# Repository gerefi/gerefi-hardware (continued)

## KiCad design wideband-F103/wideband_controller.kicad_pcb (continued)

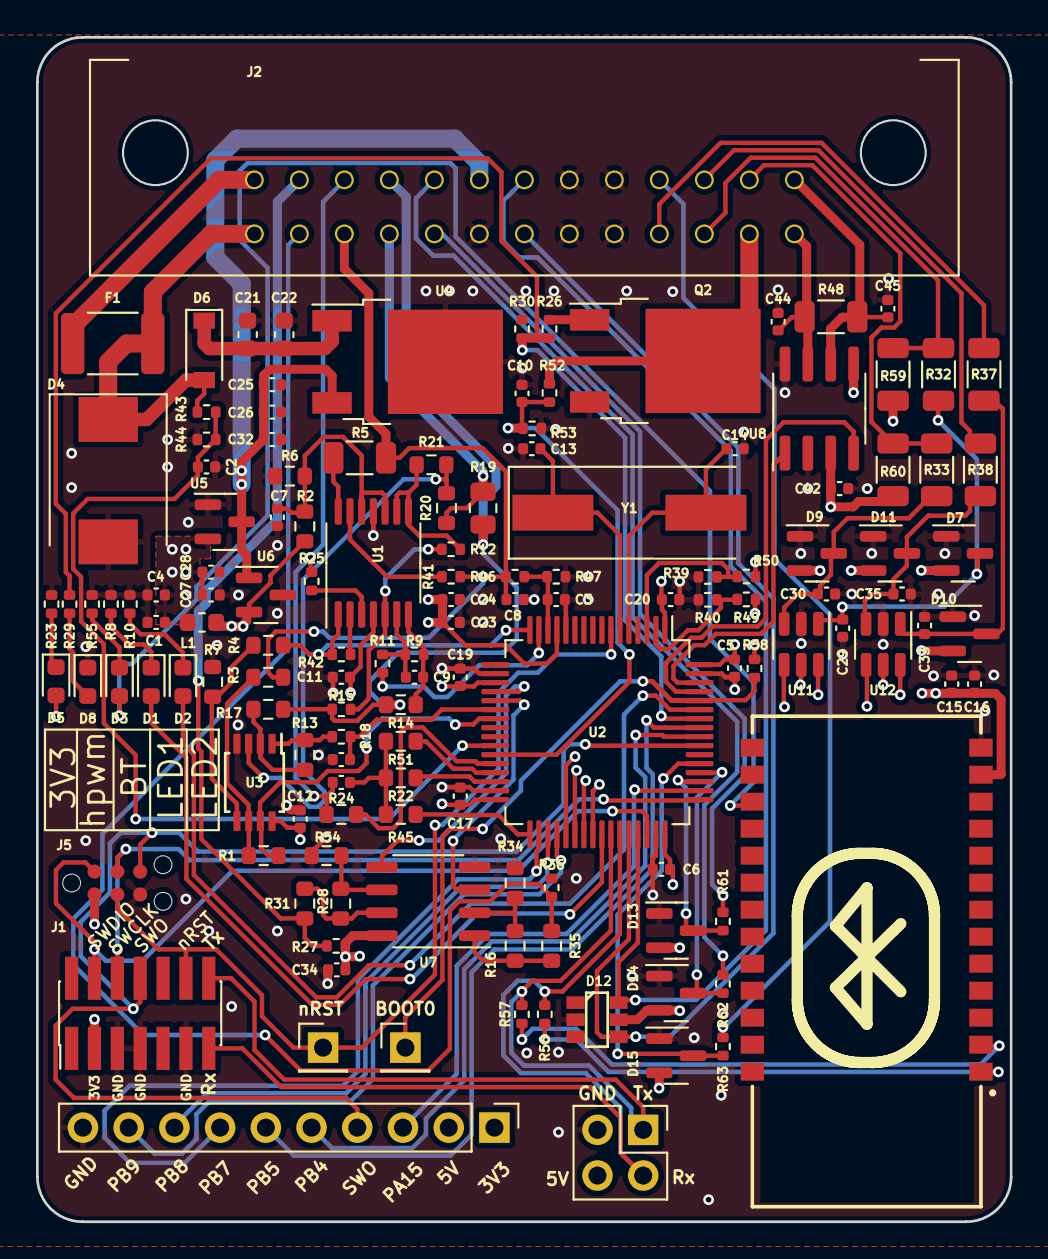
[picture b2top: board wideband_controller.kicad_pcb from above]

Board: 4 copper layers, 54.1 x 65.8 mm, 138 parts (0 on the bottom side), 99 nets.

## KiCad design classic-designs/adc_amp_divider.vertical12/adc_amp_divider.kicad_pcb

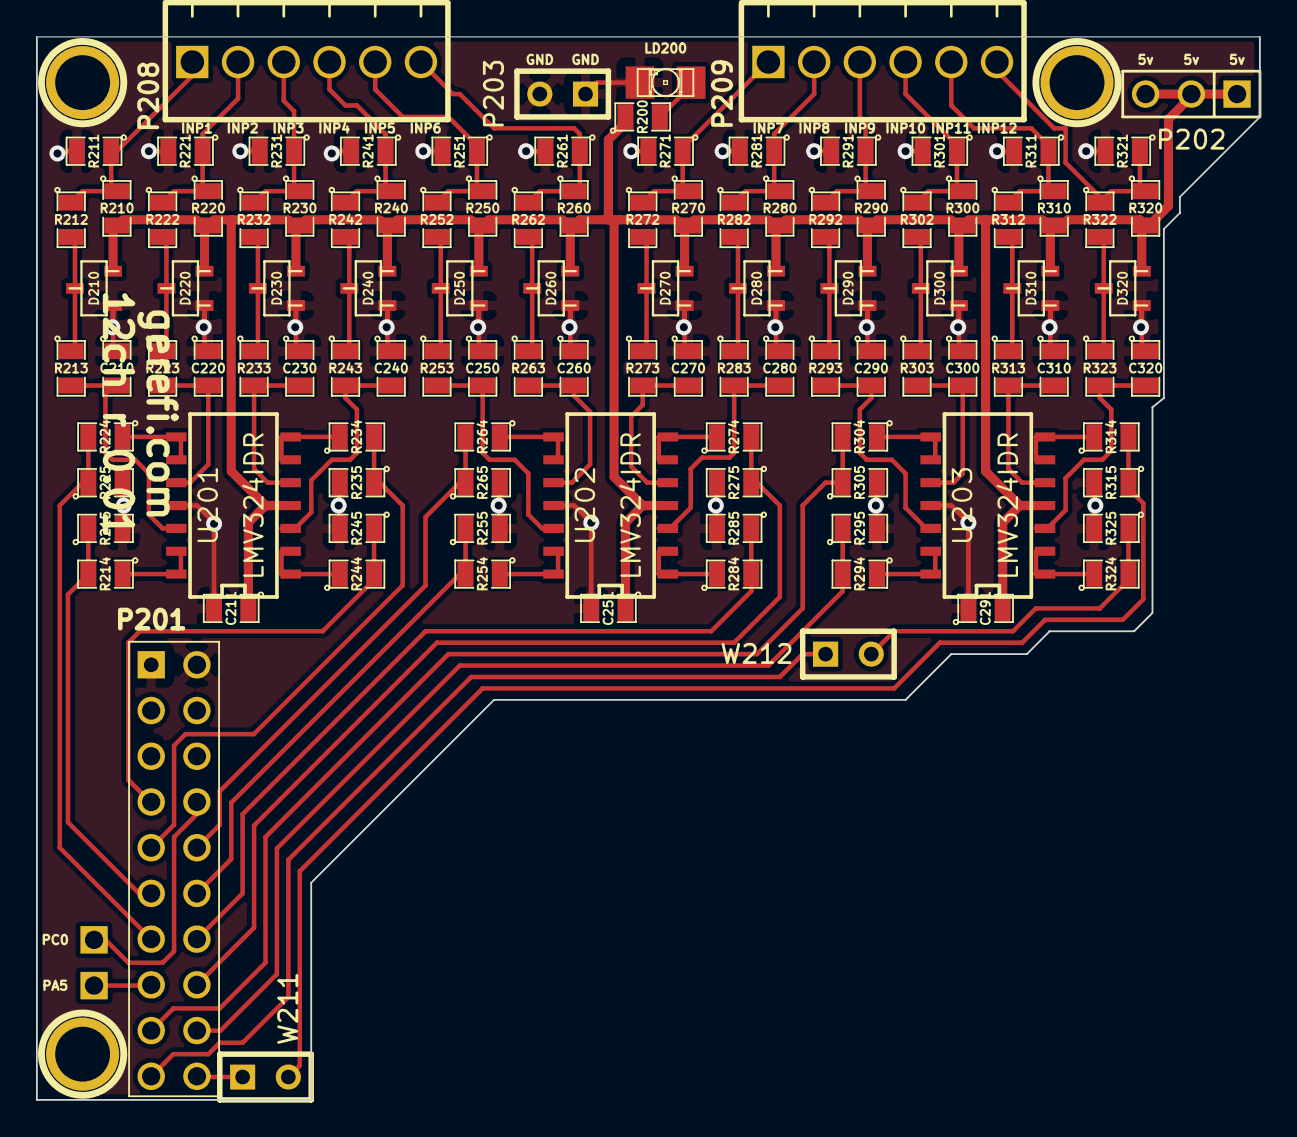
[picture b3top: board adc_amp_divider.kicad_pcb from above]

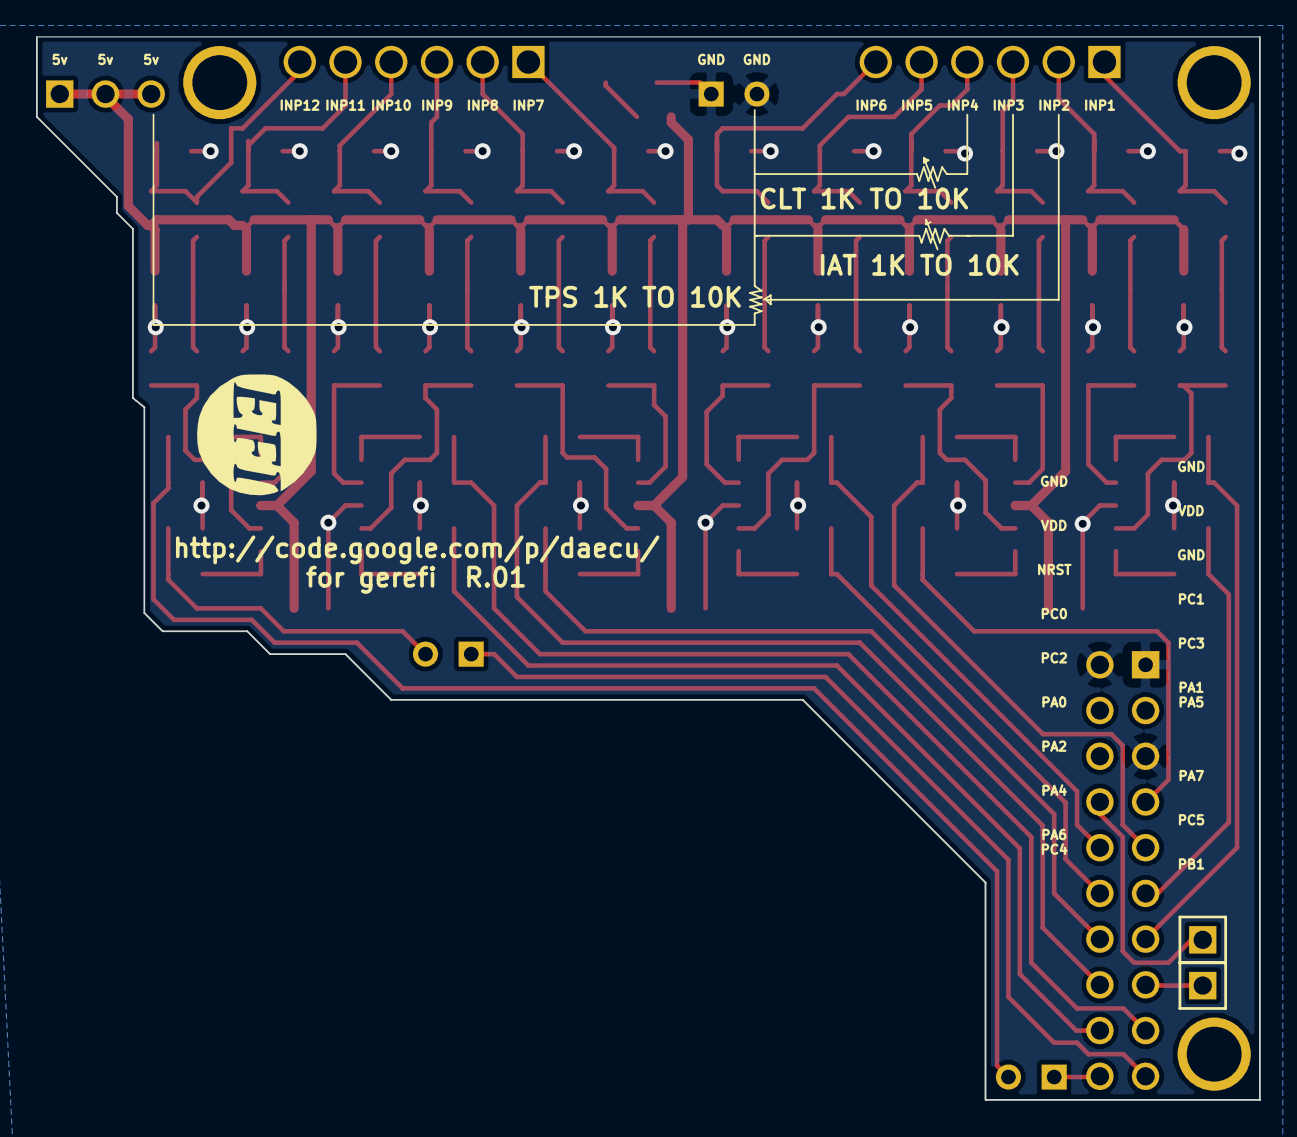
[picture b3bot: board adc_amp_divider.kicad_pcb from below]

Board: 2 copper layers, 67.9 x 59.1 mm, 117 parts (3 on the bottom side), 67 nets.

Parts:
C210, C220, C230, C240, C250, C260, C270, C280, C290, C300, C310, C320: 0.01uF; SM0805
C211, C251, C291: 0.1uF; SM0805
D210, D220, D230, D240, D250, D260, D270, D280, D290, D300, D310, D320: DOUBLE_SCHOTTKY; sot23
G201: LOGO; LOGO_F
LD200: LED; LED-1206
M200, M201, M202: CONN_1; 1pin
P201: CONN_10X2; PIN_ARRAY_10X2_M
P202: CONN_3; PIN_ARRAY_3X1
P203: CONN_2; SIL-2
P204, P205: CONN_1; PIN_ARRAY_1
P208, P209: CONN_6; 6_screw_term_.1in
R200, R213, R223, R233, R243, R253, R263, R273, R283, R293, R303, R313, R323: 100; SM0805
R210, R220, R230, R240, R250, R260, R270, R280, R290, R300, R310, R320: 2700; SM0805
R211, R221, R231, R241, R251, R261, R271, R281, R291, R301, R311, R321: 500K; SM0805
R212, R222, R232, R242, R252, R262, R272, R282, R292, R302, R312, R322: 10k; SM0805
R214, R215, R224, R225, R234, R235, R244, R245, R254, R255, R264, R265, R274, R275, R284, R285, R294, R295, R304, R305, R314, R315, R324, R325: 1500; SM0805
U201, U202, U203: LMV324IDR; SO14N
W211, W212: TEST; SIL-2

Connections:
/5V: C211.1, C251.1, C291.2, D210.3, D220.3, D230.3, D240.3, D250.3, D260.3, D270.3, D280.3, D290.3, D300.3, D310.3, D320.3, P202.1, P202.2, P202.3, R200.1, R210.2, R220.2, R230.2, R240.2, R250.2, R260.2, R270.2, R280.2, R290.2, R300.2, R310.2, R320.2, U201.4, U202.4, U203.4
/INP1: P208.1, R210.1, R211.1, R212.1
/INP2: P208.2, R220.1, R221.1, R222.1
/INP3: P208.3, R230.1, R231.1, R232.1
/INP4: P208.4, R240.1, R241.1, R242.1
/INP5: P208.5, R250.1, R251.1, R252.1
/INP6: P208.6, R260.1, R261.1, R262.1
/INP7: P209.1, R270.1, R271.1, R272.1
/INP8: P209.2, R280.1, R281.1, R282.1
/INP9: P209.3, R290.1, R291.1, R292.1
/INP10: P209.4, R300.1, R301.1, R302.1
/INP11: P209.5, R310.1, R311.1, R312.1
/INP12: P209.6, R320.1, R321.1, R322.1
/OUT1: P201.11, R214.2, R215.1
/OUT2: P201.13, R224.2, R225.1
/OUT3: P201.9, R234.2, R235.1
/OUT4: P201.7, R244.2, R245.1
/OUT5: P201.12, R254.2, R255.1
/OUT6: P201.10, R264.2, R265.1
/OUT7: P201.16, R274.2, R275.1
/OUT8: P201.14, R284.2, R285.1
/OUT9: P201.18, R294.2, R295.1
/OUT10: P201.17, R304.2, R305.1
/OUT11: P201.20, W211.1
/OUT12: P201.19, W212.1
/PA5: P201.15, P204.1
/PC0: P201.8, P205.1
GND: C210.1, C211.2, C220.1, C230.1, C240.1, C250.1, C251.2, C260.1, C270.1, C280.1, C290.1, C291.1, C300.1, C310.1, C320.1, D210.1, D220.1, D230.1, D240.1, D250.1, D260.1, D270.1, D280.1, D290.1, D300.1, D310.1, D320.1, LD200.2, P201.1, P201.2, P201.5, P203.1, P203.2, R211.2, R215.2, R221.2, R225.2, R231.2, R235.2, R241.2, R245.2, R251.2, R255.2, R261.2, R265.2, R271.2, R275.2, R281.2, R285.2, R291.2, R295.2, R301.2, R305.2, R311.2, R315.2, R321.2, R325.2, U201.11, U202.11, U203.11
unnamed: D250.2, R252.2, R253.1
unnamed: D260.2, R262.2, R263.1
unnamed: D210.2, R212.2, R213.1
unnamed: D220.2, R222.2, R223.1
unnamed: D280.2, R282.2, R283.1
unnamed: R214.1, U201.13, U201.14
unnamed: R224.1, U201.8, U201.9
unnamed: D270.2, R272.2, R273.1
unnamed: R244.1, U201.1, U201.2
unnamed: D300.2, R302.2, R303.1
unnamed: D290.2, R292.2, R293.1
unnamed: R304.1, U203.8, U203.9
unnamed: R294.1, U203.13, U203.14
unnamed: C290.2, R293.2, U203.12
unnamed: C300.2, R303.2, U203.10
unnamed: R314.1, U203.6, U203.7
unnamed: R324.1, U203.1, U203.2
unnamed: C310.2, R313.2, U203.5
unnamed: C320.2, R323.2, U203.3
unnamed: D320.2, R322.2, R323.1
unnamed: D310.2, R312.2, R313.1
unnamed: R324.2, R325.1, W212.2
unnamed: R314.2, R315.1, W211.2
unnamed: C250.2, R253.2, U202.12
unnamed: R254.1, U202.13, U202.14
unnamed: R274.1, U202.6, U202.7
unnamed: R264.1, U202.8, U202.9
unnamed: C240.2, R243.2, U201.3
unnamed: C230.2, R233.2, U201.5
unnamed: C270.2, R273.2, U202.5
unnamed: C280.2, R283.2, U202.3
unnamed: C220.2, R223.2, U201.10
unnamed: C210.2, R213.2, U201.12
unnamed: C260.2, R263.2, U202.10
unnamed: R284.1, U202.1, U202.2
unnamed: D240.2, R242.2, R243.1
unnamed: LD200.1, R200.2
unnamed: D230.2, R232.2, R233.1
unnamed: R234.1, U201.6, U201.7

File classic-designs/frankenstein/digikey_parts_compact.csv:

### this file was generated by gerefi bom_builder on Sat Feb 22 11:01:39 CST 2014
### 292 components in 2047 lines of frankenstein.cmp
### 65 kinds of components in input file
### 9 entries in BOM dictionary bom_dictionary_digikey.csv
### 2 entries in ignore list
### no BOM record for 1pin_CONN_1
### no BOM record for LED-0805_GREEN
### no BOM record for LED-0805_LED
### no BOM record for LED-0805_RED
### no BOM record for LED-1206_LED
### no BOM record for MICRO-SDCARD-CONNECTOR-3300060P1_MICRO-SDCARD-CONNECTOR-3300060P1
### no BOM record for OSTVN06A150_CONN_6
### no BOM record for PIN_ARRAY-6X1_CONN_6
### no BOM record for PIN_ARRAY_10X2_CONN_10X2
### no BOM record for PIN_ARRAY_10X2_M_CONN_10X2
### no BOM record for PIN_ARRAY_1_CONN_1
### no BOM record for PIN_ARRAY_2X1_CONN_2
### no BOM record for PIN_ARRAY_2_A_CONN_2
### no BOM record for PIN_ARRAY_2_A_JUMPER
### no BOM record for PIN_ARRAY_3X1_CONN_3
### no BOM record for PIN_ARRAY_3_A_CONN_3
### no BOM record for PIN_ARRAY_4x1_CONN_4
### no BOM record for PIN_ARRAY_5x2_CONN_5X2
### no BOM record for SIL-16_3.5MM_CONN_16
### no BOM record for SIL-2_0R
### no BOM record for SIL-2_CONN_2
### no BOM record for SIL-2_DIODE
### no BOM record for SIL-2_JUMPER
### no BOM record for SIL-2_OPT
### no BOM record for SIL-2_TEST
### no BOM record for SM0805_.1uF
### no BOM record for SM0805_0.01uF
### no BOM record for SM0805_0.1uF
### no BOM record for SM0805_100
### no BOM record for SM0805_1000pF
### no BOM record for SM0805_10K
### no BOM record for SM0805_10k
### no BOM record for SM0805_10uF
### no BOM record for SM0805_120
### no BOM record for SM0805_1500
### no BOM record for SM0805_1K
### no BOM record for SM0805_1M
### no BOM record for SM0805_1uF
### no BOM record for SM0805_20K
### no BOM record for SM0805_2700
### no BOM record for SM0805_4.7uF
### no BOM record for SM0805_4700pF
### no BOM record for SM0805_47pF
### no BOM record for SM0805_500K
### no BOM record for SM0805_5k
### no BOM record for SM0805_LED
### no BOM record for SM1206_LED
### no BOM record for SOD-123_DIODE
### no BOM record for bornier3_CONN_3
### no BOM record for pin_array_10x2_CONN_10X2
### no BOM record for pin_array_3x2_CONN_3X2
### no BOM record for pin_array_4x2_CONN_4X2
### no BOM record for sot23_DOUBLE_SCHOTTKY
### no BOM record for uMAX-uSOP_10_MAX9939




1,670-1190-1-ND,mini USB socket
4,P1.0KACT-ND,some reference
12,P20.0CCT-ND,driver current limiting
1,296-11654-1-ND,CAN driver
12,497-11082-1-ND,12A low-side MOSFET
1,MAX9926UAEE+TCT-ND,VR chip
3,TC4427AVOA-ND,1.5A dual driver
3,497-4943-1-ND,quad op-amp
1,768-1007-1-ND,USB TTL chip

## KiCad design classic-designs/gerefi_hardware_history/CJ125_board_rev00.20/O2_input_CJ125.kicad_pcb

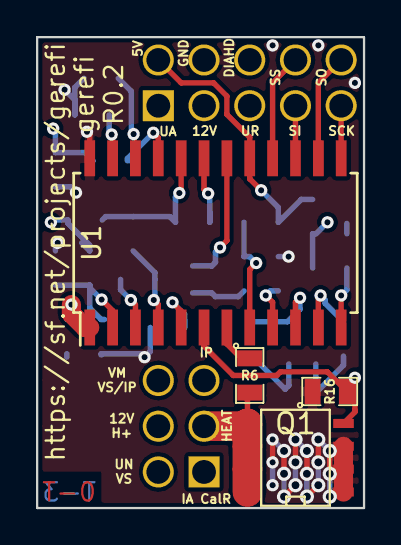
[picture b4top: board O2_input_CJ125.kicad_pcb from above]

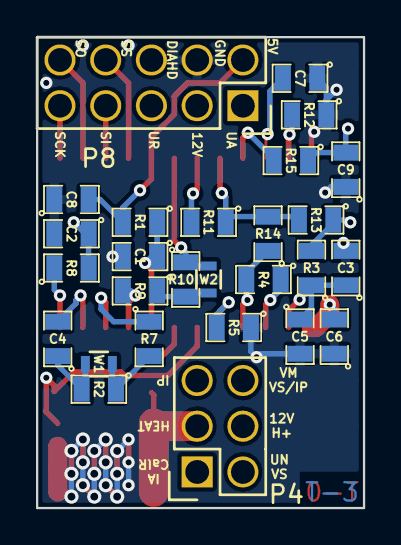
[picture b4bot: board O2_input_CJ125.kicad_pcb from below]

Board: 4 copper layers, 18.2 x 26.2 mm, 31 parts (27 on the bottom side), 31 nets.

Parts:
C1: 1000pF; SM0805
C2, C6, C8: 0.033uF; SM0805
C3, C4, C7: 0.1uF; SM0805
C5: 220pf; SM0805
C9: 0.01uF; SM0805
P4: CONN_02X03; Socket_Strip_Straight_2x03
P8: CONN_02X05; Socket_Strip_Straight_2x05
Q1: FDS2734; SO8E_ST
R1, R5, R7, R16: 10k; SM0805
R2: 21k6; SM0805
R3: 160; SM0805
R4: 61.9; SM0805
R6: 6.8k; SM0805
R8, R15: 1k; SM0805
R9: 82.5; SM0805
R10: 117.5; SM0805
R11: 4.7k; SM0805
R12, R13: 100k; SM0805
R14: 470k; SM0805
U1: CJ125; SOIC-24_7.5x15.4mm_Pitch1.27mm
W1, W2: TEST; R_0603

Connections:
/CF: C7.2, U1.22
/CJ125_5v: C8.2, P8.2, R1.2, U1.17
/CJ125_HEATER: P4.3, Q1.2, R6.2
/CJ125_IA: P4.1, R4.2, R14.1, U1.4
/CJ125_IP: P4.5, R4.1, U1.3
/CJ125_SCK: P8.9, U1.13
/CJ125_SI: P8.7, U1.15
/CJ125_SO: P8.10, U1.14
/CJ125_SS: P8.8, U1.16
/CJ125_UA: C9.2, P8.1, R15.1
/CJ125_UN: P4.2, R3.2, R13.1
/CJ125_UR: C2.1, P8.5, R8.2
/CJ125_VM: P4.6, R10.1, U1.18, W2.2
/CM: C4.2, U1.11
/DIAHD: R6.1, U1.7
/DIAHG: P8.6, Q1.1, R16.2, U1.6
/OSZ: R5.2, U1.5
/RF: R12.2, U1.23
/RM: R7.1, U1.10
/RS: R9.2, U1.9
/RST: C1.1, R1.1, U1.8
/UA: R15.2, U1.21
/UN: C3.1, C5.1, R3.1, U1.2
/UP: R11.1, R13.2, R14.2, U1.20
/UR: R8.1, U1.12
/US: R11.2, U1.19
/WO2-12V: C6.2, P4.4, P8.3, U1.1
GND: C1.2, C2.2, C3.2, C5.2, C6.1, C7.1, C8.1, C9.1, P8.4, Q1.3, R5.1, R12.1, R16.1, U1.24
unnamed: C4.1, R2.2, W1.1
unnamed: R2.1, R7.2, W1.2
unnamed: R9.1, R10.2, W2.1

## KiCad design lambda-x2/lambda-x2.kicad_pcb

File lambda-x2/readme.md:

# About

* STM32F103 dual channel wideband AFR controller supporting Bosch LSU4.9 and LSU4.2 (LSU_ADV work in progress)
* CAN and analog output
* x2 EGT input using MAX31855KASA or MAX31856
* x2 auxilary analog input: 0..5V with pull-up or pull-down (configurable by soldering resistor). One can be used to source 5V to external sensor.
* x2 2 auxilary output 0..5V. Also can be used for slow PWM signal output.
* x2 open drain outputs: BTS3028 (5A)
* Bluetooth or USRT TunerStudio connectivity
* MegaSquirt compatible pass-through connection over CAN http://www.msgpio.com/manuals/mshift/cpt.html (in progress)

See [interactive pinout](https://gerefi.com/docs/pinouts/lambda-x2/)

See [wire colors](https://github.com/gerefi/gerefi/wiki/WBO#naming-convention) for standart LSU wire collors and connectors pinouts.

For firmware see https://github.com/dron0gus/wideband (based on https://github.com/mck1117/wideband)

See gerefi forum: [F103 dual channel wideband controller + EGT + 2 x AUX In + 2 Aux out](https://gerefi.com/forum/viewtopic.php?f=4&t=2314)

See also https://github.com/gerefi/gerefi/wiki/WBO

# Known issues

## DFU mode/floating PB2

BOOT0 = 1, BOOT1 = 0 pattern is used to enter DFU bootloader on power/reset. BOOT0 is controled by jumper/button. BOOT1 (PB2) is used as bias current source for LSU4.9 and floating.

Use jumper wire to connect PB2 (through bias resistor) to GND: connect A2 pin of main connector with GND (J4 AUX connector pin 10)

## ESR measurement crosstalk between channels (rev0 and rev1)

HW has three different outputs for Nernst cell ESR measurement with different output resistance: 6.8K for LSU4.2, 22K for LSU4.9 and 47K for LSUADV. Idea was to allow the user to set the type of sensor from SW only.

Each ESR output is driven by one MCU GPIO. GPIOs for unused ESR measurement outputs are kept in Hi-Z (input) state and does not affect ESR measurement.

Same GPIO drivers ESR outputs for both channels. **This is the root cause of problem**

Problem: unused ESR output with GPIO in Hi-Z state connect Nernst cell outputs from left and right channel through two resistors. This causes crosstalk between channels and inaccurate ESR measurement. Wrong ESR measurement causes incorrect sensor temperature calculation. This can lead to inaccurate AFR measurement, overheating or underheating of the sensor.

Same issue for LSU4.9 bias resistors R22 and R70.

Solution:

Boards come with all ESR drive resistors populated. You have to remove unnecessary resistors.

If LSU4.2 sensor is used: remove R24, R25, R71, R72, R22, R70. Keep R41 and R73 - 6.8K

If LSU4.9 sensor is used: remove R25, R41, R72, R73. Keep R24 and R71 - 22K

If LSUADV sensor is used: remove R24, R41, R71, R73, R22, R70. Keep R25 and R72 - 47K

This will be (or not) solved in next revision of HW.

# Pinout

## Connectors pinout

[Main connector interactive Pinout](https://gerefi.com/docs/pinouts/lambda-x2/)

J4 is AUX connector available on PCB. SPI and I2C interfaces along with 3.3V and 5V are routed to this connector. Can be used to connect some small disply (SW not implemented yet)

J3 connector is for flashing and powering board on table. Also can be used for TunerStudion connection.

J1 and J2 are JTAG connectos.

## Uart pinout

J3 connector. Colors are default for cheap usb-to-uart converters based on CP2101 or FTDI232
Connect red wire if you want to power device from USB.
Default baud rate is 115200.

# Bluetooth

No extra steps needed to initialize JDY-33. Default device name is "gerefi WBO x2" (or "gerefi WBO x2 BLE" for BT BLE)

Default baud rate is 115200.

# TunerStudio configuration

Baudrate is 115200
[.ini file](https://github.com/dron0gus/wideband/blob/master/firmware/ini/gerefi_wb_f1_dual.ini) for both UART and BT connection.

Both interfaces can be used simultaneously for data logging but not for settings change (from rev1).

Rev0 share same UART for both interfaces.

# Firmware Upload

Two ways to program using STM32CubeProgrammer

* recommended way: using UART connectivity. Power device up while shorting BOOT0 jumper to enter DFU mode.
* st-link if you have tc2030 spring-loaded cable.
* update over CAN or UART (J3) using OpenBLT (update over BT is in progress)

TL,DR: 9600 nothing connected on main connector

## Updating over UART using DFU mode

1. Disconnect main connector. If you are going to apply +12V power through main connector - make sure that nothing else is connected to WBO (LSU sensors, any load, etc). But I recommend flash using +5V from USB.
   
3. connect USB to uart connector to J3 connector: gnd, rx and tx.
Don't forget to cross Rx-`Tx (adapter's Tx goes to WBO's Rx, WBO's Tx goes to adapter's Rx).
If you going to power WBO from USB port - also attach 5V line. Do not connect +5 from USB adapter if you are going to use +12V supply through main connector. 

3. Download and install STM32 Flash Loader Demonstrator. (Alternative tool is stm32flash - not covered in this instruction)

5. Figure out USB to serial serial port number: 

5. Start Flash Loader Demonstrator GUI application, select correct COM port. Optional: reduce timeout to 1 second:

6. Press and hold BOOT0 button on the bottom of PCB. Or short BOOT0 PCB jumper if button is not populated on your board.

8. Apply power (while holding BOOT0 button) to board and press Next in application.
After app detects chip you should see something similar to:

8. Press next, select "Download to device", select wideband.bin file.
Select "Jump to user application" and "Verify after download"

9. Press Next and wait for flash/verification ends.

## Updating using JTAG

DBD.

## Update using OpenBLT

OpenBLT https://www.feaser.com/openblt/doku.php

1. Restart device to OpenBLT mode using "Reset to OpenBLT" button under Controller -> ECU tools in TunerStudio.
   
2. Close TunerStudio to release serial port

3. Open BootCommander, select correct serial port, select wideband_update.srec file.

# Changelog

## rev 1
* Switch to 64 pin STM32/GD32
* Add 8MHz HSE oscillator (better clock stability for CAN over wide temperature range)
* Use DAC (instead of PWM) outputs for driving Ip
* Move BT to UART3/USART3, keep USART1 for bootloader/debug
* Drive BT's EN signal from MCU
* Fix RC filters on heater outputs for better voltage measurement
* Use separate ADC input for Vbat measurement
* Use ADC channels for AUX outputs monitoring/diagnostic
* Use PWM noise cancelation circuit on AUX analog outputs
* Removed useless/non-functional protection of Vm outputs
* Fix board outline to fit two types of enclosure ("plastic top" and "alloy brick")
* Add testpoints for TC2030 JTAG probe
* Add buttons for Reset and Boot0
* Add Cfg1 and jumpers
* Replace fuse holder with resettable 0.2A 33V fuse
* Two status LEDs for separate status indication for left and right channel
* Silkscreen labels around testpoints
* Silkscreen labels at uart connector on both sides of PCB
* Un_3x_sense formula is now 0.247 + 3.15 * (Un - Vm)
* Un_sense (not gained) is also routed to ADC input
* Protection from possible Ip current when MCU in reset/bootloader
* White "power on" LED replaced with green
* Main connector pinout added to top silkscreen
* AUX connector pinout added to top silkscreen

## rev 0

Seems to work with proper C10/C35 using https://github.com/gerefi/wideband/releases/tag/20230210-does-not-match-binaris

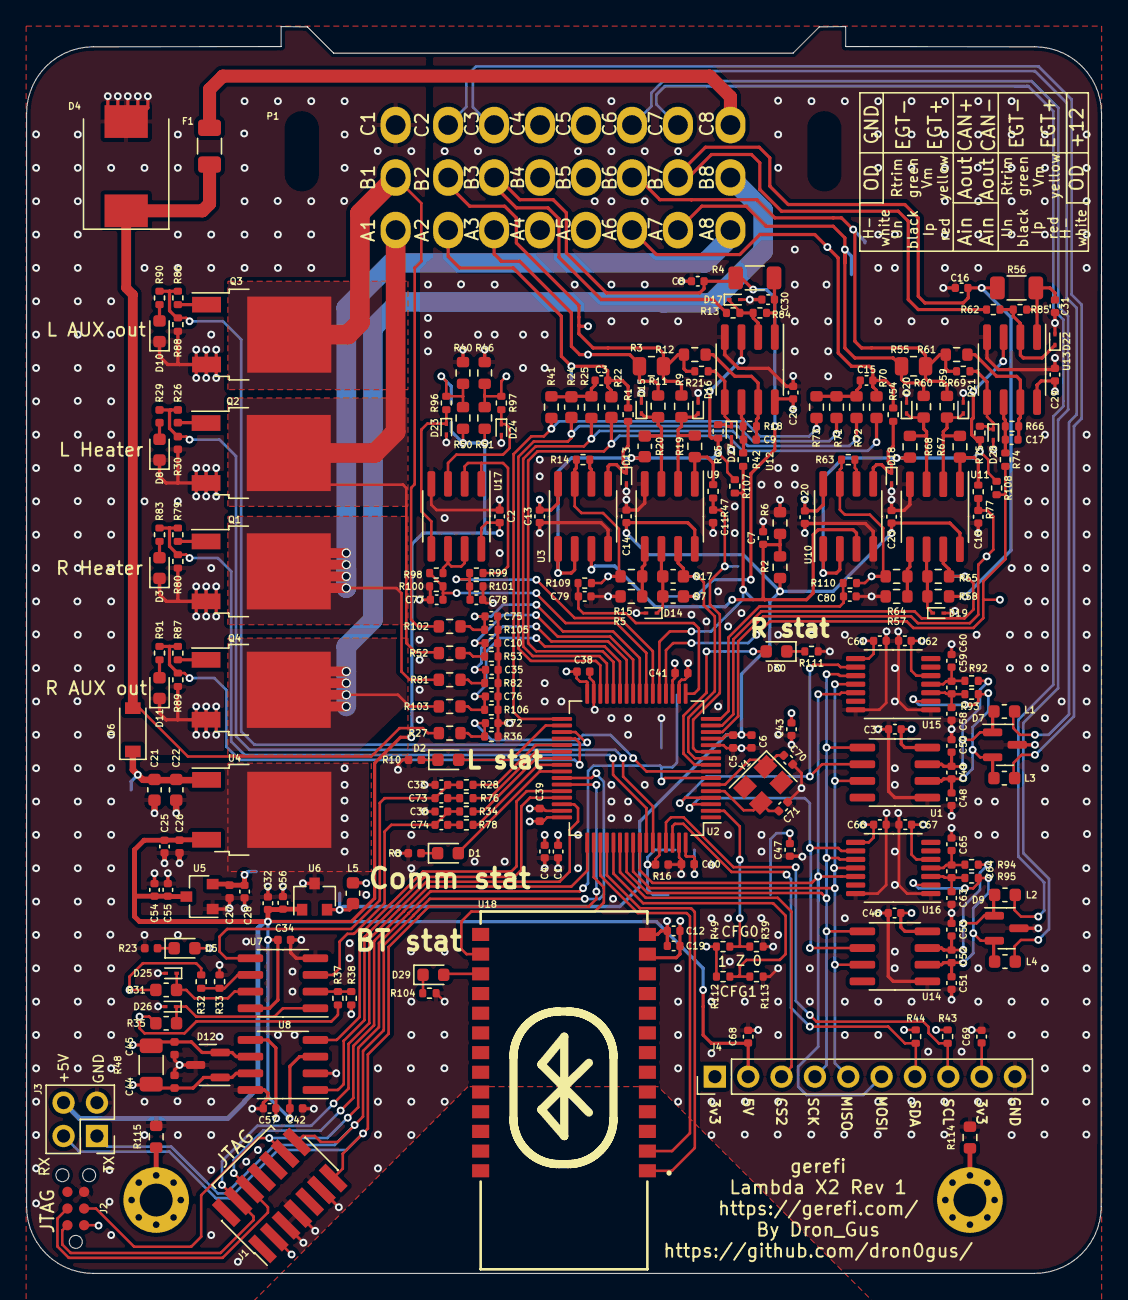
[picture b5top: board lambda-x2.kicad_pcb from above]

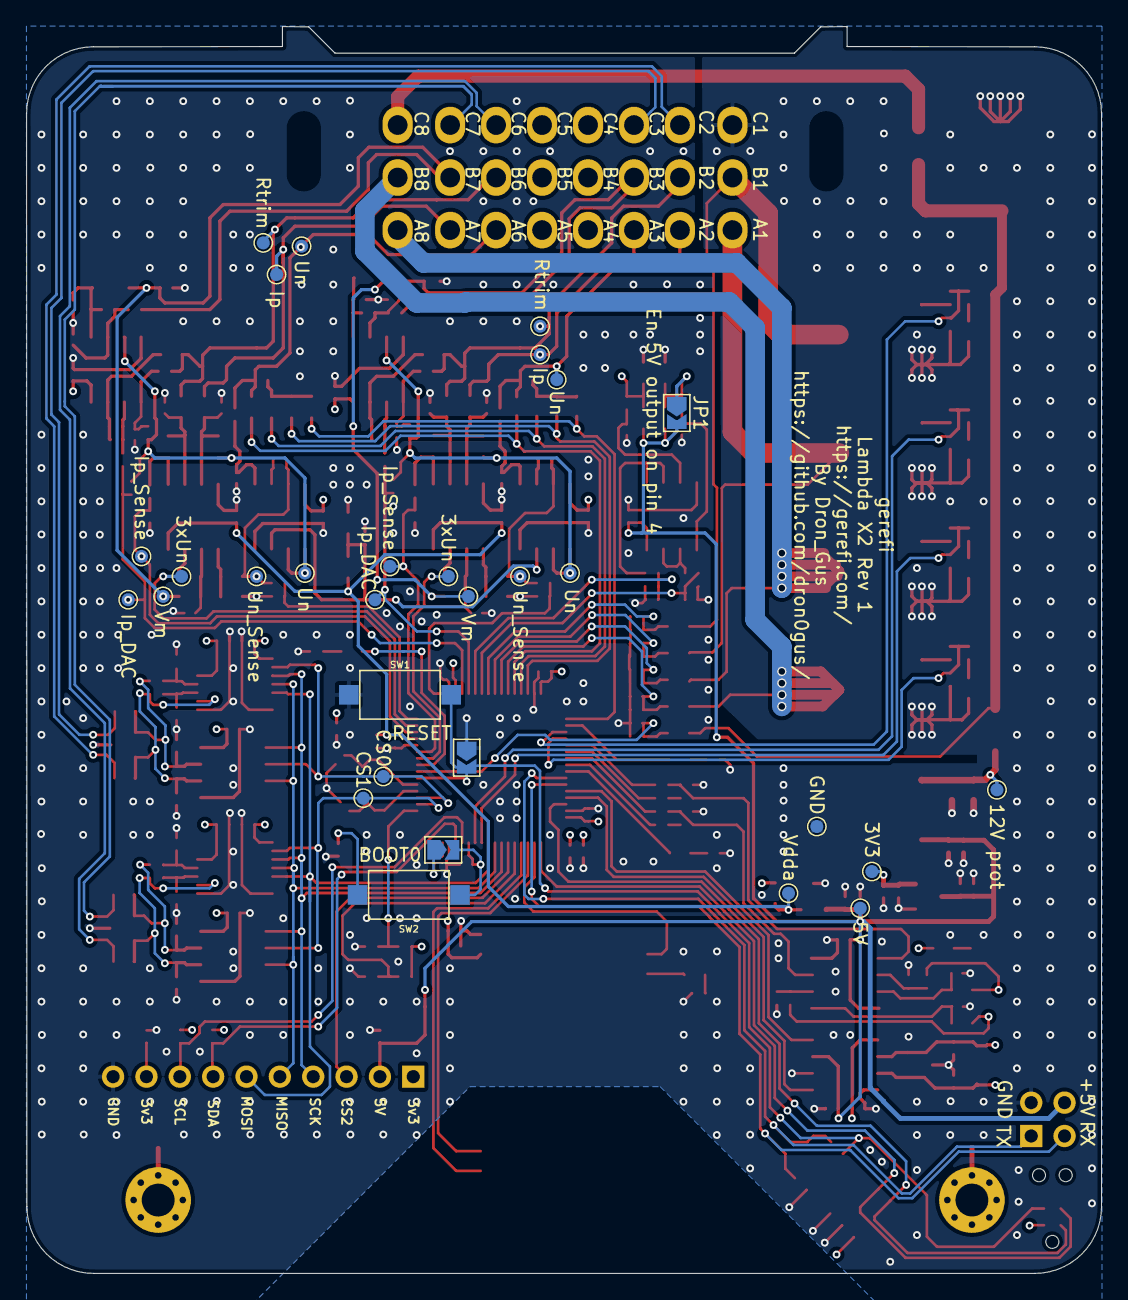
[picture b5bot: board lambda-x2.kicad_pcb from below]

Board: 4 copper layers, 81.9 x 95.0 mm, 291 parts (30 on the bottom side), 149 nets.

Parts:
C1, C6, C7, C8, C12, C16, C25, C28, C30, C31, C32, C43, C47, C54: 1u; C_0402_1005Metric
C2, C3, C5, C11, C13, C14, C15, C18, C19, C20, C23, C24, C26, C27, C29, C33, C34, C36, C37, C38, C39, C40, C41, C42, C46, C49, C52, C55, C56, C57, C59, C61, C62, C64, C66, C67, C68, C69, C73, C74: 100n; C_0402_1005Metric
C4: 4.7u; C_0402_1005Metric
C9, C17: 33n; C_0402_1005Metric
C10, C35, C72, C75, C76, C77, C78, C79, C80: 1n; C_0402_1005Metric
C21: 1u 25V; C_0603_1608Metric
C22: 100n 25V; C_0603_1608Metric
C44, C45: 47p; C_0402_1005Metric
C48, C50, C51, C53, C58, C60, C63, C65: 10nF 50V; C_0402_1005Metric
C70, C71: 20pF 50V; C_0402_1005Metric
D1: BLUE; LED_0603_1608Metric
D2, D5, D29, D30: GREEN; LED_0603_1608Metric
D3, D8, D10, D11: RED; LED_0603_1608Metric
D4: SMCJ22CA; D_SMC
D6: 1N4148W; D_SOD-123
D7, D9, D12: NUP2105L; SOT-23
D13, D14, D15, D16, D17, D18, D19, D20, D21, D22, D23, D24, D25, D26, D27, D28: ESD5V0D9B; D_SOD-923
F1: BSMD1206-025-33V; Fuse_1206_3216Metric
H1, H4: MountingHole_Pad; MountingHole_2.5mm_Pad_Via
J1: FTSH-107-01-F-DV-K; PinHeader_2x07_P1.27mm_Vertical_SMD
J2: tc2030-idc-nl
J3: Conn_02x02_Odd_Even; PinHeader_2x02_P2.54mm_Vertical
J4: Conn_01x10; PinHeader_1x10_P2.54mm_Vertical
JP1, JP2, JP3: SolderJumper_2_Open; SolderJumper-2_P1.3mm_Open_TrianglePad1.0x1.5mm
L1, L2, L3, L4, L5: 470R@100MHz; L_0603_1608Metric
P1: 33311-24AW-2
Q1, Q2, Q3, Q4: BTS3028; TO-252-2
R1, R14, R16, R18, R21, R30, R49, R54, R63, R66, R69, R80, R88, R89, R96, R97, R107, R108, R112: 10k; R_0402_1005Metric
R2, R5, R6, R7, R9, R11, R57, R58, R59, R60: 10k 0.1%; R_0603_1608Metric
R3, R55: 61.9R 1%; R_0805_2012Metric
R4, R56: 10R; R_1206_3216Metric
R8, R10, R23, R26, R29, R79, R83, R86, R87, R90, R91, R104, R109, R110, R111: 1k; R_0402_1005Metric
R12, R61, R114, R115: 47R; R_0603_1608Metric
R13, R36, R53, R62, R82, R84, R85, R105, R106: 10k 1%; R_0402_1005Metric
R15, R64: 2.7k 0.1%; R_0603_1608Metric
R17, R65: 30k 1%; R_0603_1608Metric
R19, R20, R67, R68: 100k 0.1%; R_0603_1608Metric
R22, R70: 62k 1%; R_0603_1608Metric
R24, R71: 22k 0.1%; R_0603_1608Metric
R25, R72: 47k 1%; R_0603_1608Metric
R27, R52, R81, R102, R103: 100k 1%; R_0603_1608Metric
R28, R34, R43, R44, R47, R76, R77, R78: 3.3k; R_0402_1005Metric
R31, R35: 330R; R_0603_1608Metric
R32, R37, R98, R99: 82k; R_0402_1005Metric
R33, R38, R100, R101: 160k; R_0402_1005Metric
R39, R113: 0R; R_0402_1005Metric
R40, R46, R50, R51: 1K; R_0603_1608Metric
R41, R73: 6.8k 0.1%; R_0603_1608Metric
R42, R45, R74, R75: 68k; R_0402_1005Metric
R48: 120R; R_1206_3216Metric
R92, R93, R94, R95: 100R; R_0402_1005Metric
SW1, SW2: SW_SPST_CK_RS282G05A3
TP3, TP4: Un_Sense; TestPoint_Pad_D1.0mm
TP5, TP6: 3xUn; TestPoint_Pad_D1.0mm
TP7: 5V; TestPoint_Pad_D1.0mm
TP8: 3V3; TestPoint_Pad_D1.0mm
TP9: Vdda; TestPoint_Pad_D1.0mm
TP10, TP17: Ip; TestPoint_Pad_D1.0mm
TP11, TP18: Rtrim; TestPoint_Pad_D1.0mm
TP12, TP19: Vm; TestPoint_Pad_D1.0mm
TP13, TP14, TP20, TP21: Un; TestPoint_Pad_D1.0mm
TP15, TP22: Ip_DAC; TestPoint_Pad_D1.0mm
TP16, TP23: Ip_Sense; TestPoint_Pad_D1.0mm
TP24: GND; TestPoint_Pad_D1.0mm
TP25: CS0; TestPoint_Pad_D1.0mm
TP26: CS1; TestPoint_Pad_D1.0mm
TP27: 12V prot; TestPoint_Pad_D1.0mm
U1, U14: MAX31855KASA; SOIC-8_3.9x4.9mm_P1.27mm
U2: STM32F103RCTx; LQFP-64_10x10mm_P0.5mm
U3, U7, U10, U12, U13, U17: MCP6002T-I/SN; SOIC-8_3.9x4.9mm_P1.27mm
U4: LM78M05_TO252; TO-252-2
U5: XC6206P332MR; SOT-23
U6: REF3033; SOT-23
U8: TJA1051T-3; SOIC-8_3.9x4.9mm_P1.27mm
U9, U11: GS8332-SR; SOIC-8_3.9x4.9mm_P1.27mm
U15, U16: MAX31856; TSSOP-14_4.4x5mm_P0.65mm
U18: JDY-33
Y1: XXDCELNANF-8MHZ; Crystal_SMD_3225-4Pin_3.2x2.5mm

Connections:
12V_RAW: F1.2, P1.24 (C8)
+3V3: C1.1, C4.1, C12.1, C13.1, C19.1, C20.1, C24.1, C27.1, C28.1, C29.1, C37.1, C38.1, C39.1, C40.1, C41.1, C43.1, C46.1, C47.1, C57.1, C61.1, C62.1, C66.1, C67.1, C69.1, D5.2 (A), J1.3, J2.1 (VCC), J4.1, J4.9, JP3.1 (A), L5.2, R43.1, R44.1, R49.2, R112.2, SW2.2, TP8.1, U1.4 (VCC), U2.19 (VDD), U2.32 (VDD), U2.48 (VDD), U2.64 (VDD), U3.8 (V+), U5.2 (VO), U8.5 (VIO), U10.8 (V+), U12.8 (V+), U13.8 (V+), U14.4 (VCC), U15.5 (AVDD), U15.8 (DVDD), U16.5 (AVDD), U16.8 (DVDD), U18.12 (3V3)
+5V: C2.1, C25.1, C26.1, C32.1, C34.1, C42.1, C54.1, C55.1, C56.1, C68.1, J3.4, J4.2, JP1.2 (B), R50.1, R51.1, TP7.1, U4.3 (VO), U5.3 (VI), U6.1 (IN), U7.8 (V+), U8.3 (VCC), U17.8 (V+)
/12V_sense: C72.1, R27.2, R36.2, U2.8 (PC0)
/BT_EN: U2.50 (PA15), U18.15 (EN)
/BT_UART_RX: U2.52 (PC11), U18.1 (TXD)
/BT_UART_TX: U2.51 (PC10), U18.2 (RXD)
/Boot0: JP3.2 (B), R16.2, SW2.1, U2.60 (BOOT0)
/CAN_H: C44.2, D12.1 (K), P1.20 (C4), R48.1, U8.7 (CANH)
/CAN_L: C45.1, D12.2 (K), P1.21 (C5), R48.2, U8.6 (CANL)
/CAN_RX: U2.44 (PA11), U8.4 (RXD)
/CAN_TX: U2.45 (PA12), U8.1 (TXD)
/DACout1: C33.1, C73.2, R28.2, U7.5 (+)
/DACout2: C36.1, C74.2, R34.2, U7.3 (+)
/I2C1_SCL: J4.8, R43.2, U2.61 (PB8)
/I2C1_SDA: J4.7, R44.2, U2.62 (PB9)
/LED_BLUE: D1.2 (A), U2.41 (PA8)
/LSU analog left/Un_sense: R14.2, R15.2, R109.1, TP3.1, U3.7
/LSU analog left/Vgnd_ref: C7.1, R2.2, R6.1, U3.3 (+), U10.3 (+)
/LSU analog right/Un_sense: R63.2, R64.2, R110.1, TP4.1, U10.7
/L_AUX: JP1.1 (A), P1.4 (A4), R40.1, R50.2, R96.1
/L_AUX_ADC: C77.1, R98.1, R100.2, U2.23 (PA7)
/L_EGT+: L1.1, P1.19 (C3)
/L_EGT-: L3.1, P1.18 (C2)
/L_Heater_sense: C10.1, R52.2, R53.2, U2.25 (PC5)
/L_Ip_dac: R42.1, R107.1, TP15.1, U2.21 (PA5)
/L_Ip_sense: C11.1, R47.1, TP16.1, U2.11 (PC3)
/L_LED_GREEN: D2.2 (A), U2.34 (PB13)
/L_LSU_Heater-: P1.1 (A1), Q2.2 (D), R52.1
/L_LSU_Ip: P1.3 (A3), R3.2, R11.2, TP10.1
/L_LSU_Rtrim: P1.10 (B2), R3.1, R9.2, R12.1, R21.1, TP11.1
/L_LSU_Un: C3.1, P1.2 (A2), R1.1, R22.2, TP13.1
/L_LSU_Vm: C8.1, P1.11 (B3), R4.1, R7.2, R13.1, TP12.1
/L_OD: P1.9 (B1), Q3.2 (D), R102.1
/L_OUT_en: R86.2, R88.2, R90.2, U2.35 (PB14)
/L_OUT_sense: C75.1, R102.2, R105.2, U2.24 (PC4)
/L_Un_3x_sense: R17.2, TP5.1, U2.10 (PC2), U9.7
/L_Un_sense: C79.1, R109.2, U2.17 (PA3)
/L_heater_pwm: R26.2, R29.2, R30.2, U2.59 (PB7)
/Nernst_4.2_esr_drive: R41.2, R73.2, U2.33 (PB12)
/Nernst_4.9_bias: R22.1, R70.1, U2.28 (PB2)
/Nernst_4.9_esr_drive: R24.2, R71.2, U2.30 (PB11)
/Nernst_ADV_esr_drive: R25.2, R72.2, U2.29 (PB10)
/R_AUX: P1.5 (A5), R46.1, R51.2, R97.1
/R_AUX_ADC: C78.1, R99.1, R101.2, U2.22 (PA6)
/R_EGT+: L2.1, P1.23 (C7)
/R_EGT-: L4.1, P1.22 (C6)
/R_Heater_sense: C35.1, R81.2, R82.2, U2.26 (PB0)
/R_Ip_dac: R74.1, R108.1, TP22.1, U2.20 (PA4)
/R_Ip_sense: C18.1, R77.1, TP23.1, U2.14 (PA0)
/R_LED_GREEN: D30.2 (A), U2.9 (PC1)
/R_LSU_Heater-: P1.8 (A8), Q1.2 (D), R81.1
/R_LSU_Ip: P1.7 (A7), R55.2, R60.2, TP17.1
/R_LSU_Rtrim: P1.14 (B6), R55.1, R59.2, R61.1, R69.1, TP18.1
/R_LSU_Un: C15.1, P1.6 (A6), R54.1, R70.2, TP20.1
/R_LSU_Vm: C16.1, P1.15 (B7), R56.1, R58.2, R62.1, TP19.1
/R_OD: P1.16 (B8), Q4.2 (D), R103.1
/R_OUT_en: R87.2, R89.2, R91.2, U2.36 (PB15)
/R_OUT_sense: C76.1, R103.2, R106.2, U2.27 (PB1)
/R_Un_3x_sense: R65.2, TP6.1, U2.15 (PA1), U11.7
/R_Un_sense: C80.1, R110.2, U2.16 (PA2)
/R_heater_pwm: R79.2, R80.2, R83.2, U2.58 (PB6)
/SPI1_CS0: TP25.1, U1.6 (~CS), U2.4 (PC15), U15.9 (~CS)
/SPI1_CS1: TP26.1, U2.3 (PC14), U14.6 (~CS), U16.9 (~CS)
/SPI1_CS2: J4.3, U2.54 (PD2)
/SPI1_MISO: J4.5, U1.7 (SO), U2.56 (PB4), U14.7 (SO), U15.11 (SDO), U16.11 (SDO)
/SPI1_MOSI: J4.6, U2.57 (PB5), U15.12 (SDI), U16.12 (SDI)
/SPI1_SCK: J4.4, U1.5 (SCK), U2.55 (PB3), U14.5 (SCK), U15.10 (SCK), U16.10 (SCK)
/SWCLK: J1.6, J2.4 (SWCLK), U2.49 (PA14)
/SWDIO: J1.4, J2.2 (SWDIO), U2.46 (PA13)
/UART_RX: J1.13, J3.2, U2.43 (PA10)
/UART_TX: J1.14, J3.1, U2.42 (PA9)
/Vout1: P1.13 (B5), R31.2, R32.2
/Vout2: P1.12 (B4), R35.2, R37.2
/config0: R39.1, R49.1, U2.2 (PC13)
/config1: R112.1, R113.1, U2.53 (PC12)
/nRESET: J1.12, J2.3 (NRESET), JP2.2 (B), SW1.2, U2.7 (NRST)
GND: C1.2, C2.2, C4.2, C5.2, C6.2, C7.2, C8.2, C10.2, C11.2, C12.2, C13.2, C14.2, C16.2, C18.2, C19.2, C20.2, C21.2, C22.2, C23.2, C24.2, C25.2, C26.2, C27.2, C28.2, C29.2, C30.2, C31.2, C32.2, C33.2, C34.2, C35.2, C36.2, C37.2, C38.2, C39.2, C40.2, C41.2, C42.2, C43.2, C44.1, C45.2, C46.2, C47.2, C48.2, C50.2, C51.2, C53.2, C54.2, C55.2, C56.2, C57.2, C58.2, C60.2, C61.2, C62.2, C63.2, C65.2, C66.2, C67.2, C68.2, C69.2, C70.1, C71.1, C72.2, C75.2, C76.2, C77.2, C78.2, C79.2, C80.2, D3.1 (K), D4.2 (A2), D7.3 (A), D8.1 (K), D9.3 (A), D10.1 (K), D11.1 (K), D12.3 (A), D13.2 (A2), D14.2 (A2), D15.2 (A2), D16.2 (A2), D17.2 (A2), D18.2 (A2), D19.2 (A2), D20.2 (A2), D21.2 (A2), D22.2 (A2), D23.2 (A2), D24.2 (A2), D25.2 (A2), D26.2 (A2), D27.2 (A2), D28.2 (A2), J1.5, J1.7, J1.11, J2.5 (GND), J3.3, J4.10, JP2.1 (A), P1.17 (C1), Q1.3 (S), Q2.3 (S), Q3.3 (S), Q4.3 (S), R5.1, R6.2, R8.1, R10.1, R16.1, R23.1, R30.1, R33.1, R36.1, R38.1, R39.2, R40.2, R46.2, R53.1, R57.1, R80.1, R82.1, R88.1, R89.1, R100.1, R101.1, R104.1, R105.1, R106.1, R111.1, R113.2, R114.2, R115.2, SW1.1, TP24.1, U1.1 (GND), U2.12 (VSSA), U2.18 (VSS), U2.31 (VSS), U2.47 (VSS), U2.63 (VSS), U3.4 (V-), U4.2 (GND), U5.1 (GND), U6.3 (GND), U7.4 (V-), U8.2 (GND), U8.8 (S), U9.4 (V-), U10.4 (V-), U11.4 (V-), U12.4 (V-), U13.4 (V-), U14.1 (GND), U15.1 (AGND), U15.14 (DGND), U16.1 (AGND), U16.14 (DGND), U17.4 (V-), U18.13 (GND)
unnamed: C3.2, R24.1, R25.1, R41.1
unnamed: C9.1, R12.2, R18.1, U12.7
unnamed: C9.2, R18.2, R42.2, U12.6 (-)
unnamed: C15.2, R71.1, R72.1, R73.1
unnamed: C17.1, R61.2, R66.1, U13.7
unnamed: C17.2, R66.2, R74.2, U13.6 (-)
unnamed: C21.1, C22.1, D6.1 (K), TP27.1, U4.1 (VI)
unnamed: C30.1, R4.2, R84.1, U12.1
unnamed: C31.1, R56.2, R85.1, U13.1
unnamed: C48.1, C49.1, D7.2 (K), L3.2, R93.1, U1.2 (T-), U15.2 (BIAS)
unnamed: C49.2, C50.1, D7.1 (K), L1.2, R92.1, U1.3 (T+)
unnamed: C51.1, C52.1, D9.2 (K), L4.2, R95.1, U14.2 (T-), U16.2 (BIAS)
unnamed: C52.2, C53.1, D9.1 (K), L2.2, R94.1, U14.3 (T+)
unnamed: C58.1, C59.1, R93.2, U15.3 (T-)
unnamed: C59.2, C60.1, R92.2, U15.4 (T+)
unnamed: C63.1, C64.1, R95.2, U16.3 (T-)
unnamed: C64.2, C65.1, R94.2, U16.4 (T+)
unnamed: C70.2, U2.6 (PD1), Y1.1
unnamed: C71.2, U2.5 (PD0), Y1.3
unnamed: C73.1, R76.2
unnamed: C74.1, R78.2
unnamed: D1.1 (K), R8.2
unnamed: D2.1 (K), R10.2
unnamed: D3.2 (A), R83.1
unnamed: D4.1 (A1), D6.2 (A), F1.1, R27.1
unnamed: D5.1 (K), R23.2
unnamed: D8.2 (A), R29.1
unnamed: D10.2 (A), R90.1
unnamed: D11.2 (A), R91.1
unnamed: D13.1 (A1), R1.2, U3.5 (+)
unnamed: D14.1 (A1), R7.1, R17.1, U9.6 (-)
unnamed: D15.1 (A1), R11.1, R20.1, U9.3 (+)
unnamed: D16.1 (A1), R9.1, R19.2, U9.2 (-)
unnamed: D17.1 (A1), R13.2, R84.2, U12.2 (-)
unnamed: D18.1 (A1), R54.2, U10.5 (+)
unnamed: D19.1 (A1), R58.1, R65.1, U11.6 (-)
unnamed: D20.1 (A1), R60.1, R68.1, U11.3 (+)
unnamed: D21.1 (A1), R59.1, R67.2, U11.2 (-)
unnamed: D22.1 (A1), R62.2, R85.2, U13.2 (-)
unnamed: D23.1 (A1), R96.2, U17.5 (+)
unnamed: D24.1 (A1), R97.2, U17.3 (+)
unnamed: D25.1 (A1), R31.1, U7.7
unnamed: D26.1 (A1), R35.1, U7.1
unnamed: D27.1 (A1), R21.2, R45.1, U12.5 (+)
unnamed: D28.1 (A1), R69.2, R75.1, U13.5 (+)
unnamed: D29.1 (K), R104.2
unnamed: D29.2 (A), U18.16 (ALED)
unnamed: D30.1 (K), R111.2
unnamed: H1.1, R114.1
unnamed: H4.1, R115.1
unnamed: Q1.1 (G), R79.1
unnamed: Q2.1 (G), R26.1
unnamed: Q3.1 (G), R86.1
unnamed: Q4.1 (G), R87.1
unnamed: R14.1, U3.6 (-)
unnamed: R5.2, R15.1, U9.5 (+)
unnamed: R19.1, R47.2, U9.1
unnamed: R28.1, U2.37 (PC6)
unnamed: R32.1, R33.2, U7.6 (-)
unnamed: R34.1, U2.39 (PC8)
unnamed: R37.1, R38.2, U7.2 (-)
unnamed: R57.2, R64.1, U11.5 (+)
unnamed: R63.1, U10.6 (-)
unnamed: R67.1, R77.2, U11.1
unnamed: R76.1, U2.38 (PC7)
unnamed: R78.1, U2.40 (PC9)
unnamed: R98.2, U17.6 (-), U17.7
unnamed: R99.2, U17.1, U17.2 (-)
unnamed: R20.2, R45.2, R107.2, TP14.1, U3.1, U3.2 (-), U12.3 (+)
unnamed: R68.2, R75.2, R108.2, TP21.1, U10.1, U10.2 (-), U13.3 (+)
VDDA: C5.1, C6.1, C14.1, C23.1, L5.1, R2.1, TP9.1, U2.13 (VDDA), U6.2 (OUT), U9.8 (V+), U11.8 (V+)

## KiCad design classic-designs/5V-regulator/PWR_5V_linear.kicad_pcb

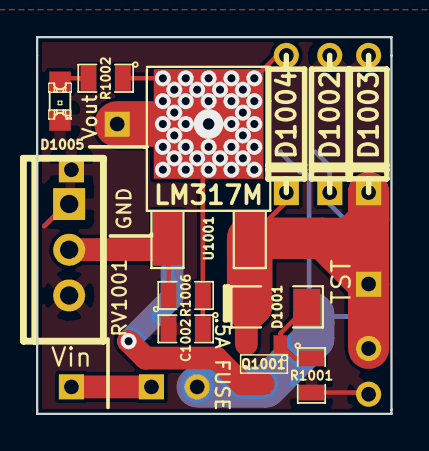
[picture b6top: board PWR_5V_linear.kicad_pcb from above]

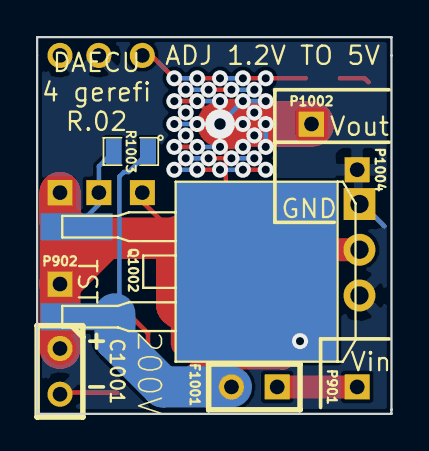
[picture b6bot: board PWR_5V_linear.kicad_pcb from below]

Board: 2 copper layers, 19.7 x 20.9 mm, 20 parts (8 on the bottom side), 10 nets.

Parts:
C1001: 0.1uF 50V; C1
C1002: 1uF 16V; SM0805
D1001: 7.5V; SM1206
D1002: 15V; D3
D1003, D1004: 24V; D3
D1005: LED-grn; LED-0805
F1001: 5A; SIL-2
P901, P902, P1002, P1004: CONN_1; SIL-1
Q1001: 30V; SOT23
Q1002: 200V; m-pad-2.1-TO-263AB
R1001, R1002: 1k; SM0805
R1003: 100k; SM0805
R1006: 240R; SM0805
RV1001: 1k; TO220_VERT
U1001: LM317M; DPAK2

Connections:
/5V-REG: C1002.1, D1004.1, P1002.1, R1002.1, R1006.2, U1001.2
/VBAT: C1001.1, D1001.2, D1003.2, D1004.2, P902.1, Q1001.2, U1001.3
/Vf: F1001.2, Q1002.3, R1003.1
/Vin: F1001.1, P901.1
/Vs1: D1002.2, Q1002.1, R1003.2
/Vs2: Q1001.3, Q1002.2
GND: C1001.2, C1002.2, D1002.1, D1003.1, D1005.2, P1004.1, R1001.2, RV1001.1, RV1001.2
unnamed: R1006.1, RV1001.3, U1001.1
unnamed: D1001.1, Q1001.1, R1001.1
unnamed: D1005.1, R1002.2
